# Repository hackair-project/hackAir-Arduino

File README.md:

hackAIR is an EU-funded project aiming to develop an open technology platform for citizen observatories on air quality. Air pollution is an environmental issue with serious health and lifespan implications. However, it remains difficult for citizens to assess their exposure to air pollution and air quality issues in their country. Official air quality sensors are often few and far between, coverage is poor outside cities, and their data is not always easily accessible.

## hackAIR Arduino Library

The hackAIR project provides resources to create your own data collection station using the Arduino platform. The library in this repository aims to support a variety of air quality sensors so anyone with some electronics knowledge can measure air quality at home and optionally submit data to the hackAIR database.

### Why Arduino

> Arduino is an open-source electronics platform based on easy-to-use hardware and software. It's intended for anyone making interactive projects. *-arduino.cc*

The Arduino platform helps create electronic project easy and fun with the only prerequisite being willing to learn and experiment. The hackAIR library takes care of the details so you can get measuring in no time.

### Sending data

While not mandatory, the library provides helpers to send air quality data over the Internet to the hackAIR platform. The official [Ethernet Shield](https://www.arduino.cc/en/Main/ArduinoEthernetShieldV2) is supported alongside the [hackAIR WiFi shield](https://github.com/hackair-project/hackAir-ArduinoWiFi), a DIY option for adding wireless connectivity to your data collection station.

### Supported Sensors

The following sensors are currently supported by the library:
 * [DFRobot PM2.5 Air Quality sensor](http://www.hackair.eu/docs/sensor-support/dfrobot/)
 * [PMS5003](http://www.hackair.eu/docs/pms5003/)
 * [SDS011](http://www.hackair.eu/docs/sds011/)
 * [PPD42NS - Grove sensor by SEEDSTUDIO](http://www.hackair.eu/docs/ppd42ns/)

### Documentation

Official documentation is available at [hackair.eu/docs/](http://www.hackair.eu/docs/). The website is continiously updated with more examples and helpful info.

### Licensing

```
hackAIR Arduino Library
Copyright © 2016-2017 hackAir Consortium

This program is free software: you can redistribute it and/or modify
it under the terms of the GNU Lesser General Public License as published
by the Free Software Foundation, either version 3 of the License, or
(at your option) any later version.

This program is distributed in the hope that it will be useful,
but WITHOUT ANY WARRANTY; without even the implied warranty of
MERCHANTABILITY or FITNESS FOR A PARTICULAR PURPOSE.  See the
GNU Lesser General Public License for more details.

You should have received a copy of the GNU Lesser General Public License
along with this program.  If not, see <http://www.gnu.org/licenses/>.
```

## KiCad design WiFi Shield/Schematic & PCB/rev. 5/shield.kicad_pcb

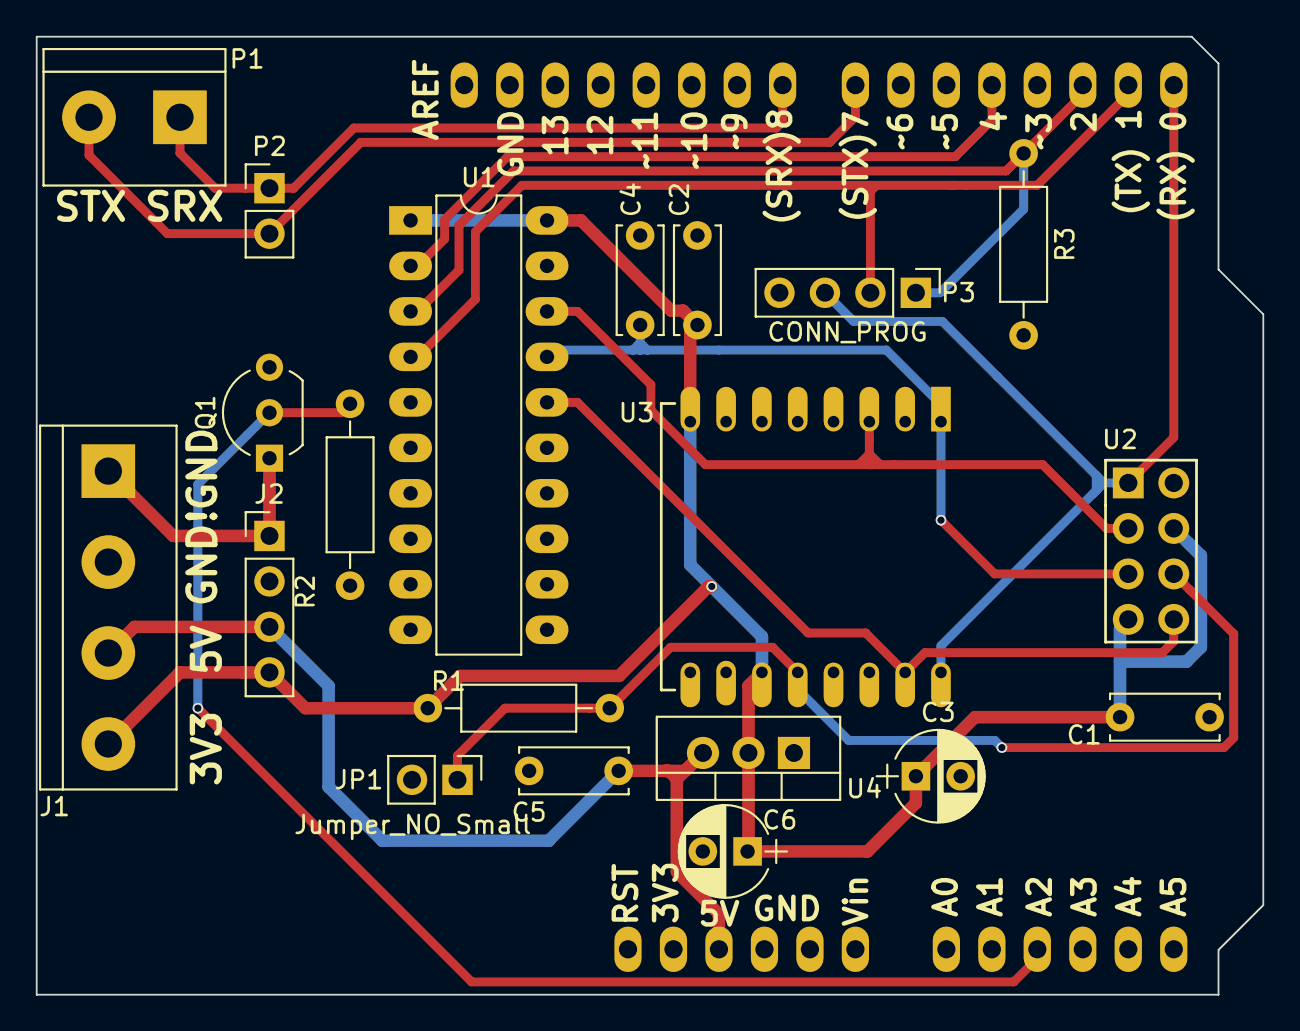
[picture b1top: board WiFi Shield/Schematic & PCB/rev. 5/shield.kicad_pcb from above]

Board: 2 copper layers, 68.5 x 53.5 mm, 21 parts (0 on the bottom side), 15 nets.

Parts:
C1, C4: 10nF; C_Disc_D6.0mm_W2.5mm_P5.00mm
C2, C5: 100nF; C_Disc_D6.0mm_W2.5mm_P5.00mm
C3, C6: 10uF; CP_Radial_D5.0mm_P2.50mm
J1: CONN_POWER; bornier4
J2: CONN_POWER_H; Pin_Header_Straight_1x04_Pitch2.54mm
JP1: Jumper_NO_Small; Pin_Header_Straight_1x02_Pitch2.54mm
P1: CONN_SENSOR_SERIAL; bornier2
P2: CONN_SENSOR_SERIAL_H; Pin_Header_Straight_1x02_Pitch2.54mm
P3: CONN_PROG; Pin_Header_Straight_1x04_Pitch2.54mm
Q1: ZVN4206A; TO-92_Inline_Wide
R1: 1K; R_Axial_DIN0207_L6.3mm_D2.5mm_P10.16mm_Horizontal
R2: 100K; R_Axial_DIN0207_L6.3mm_D2.5mm_P10.16mm_Horizontal
R3: 10k; R_Axial_DIN0207_L6.3mm_D2.5mm_P10.16mm_Horizontal
SHIELD1: ARDUINO_SHIELD; ARDUINO_SHIELD_2_040pins
U1: SN74LVC245A; DIP-20_W7.62mm_LongPads
U2: ESP-01v090; ESP-01
U3: ESP-12
U4: LD1117S33CTR; TO-220_Vertical

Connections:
+3V3: C1.1, C2.1, C3.1, C6.1, J1.4, J2.4, R1.2, U1.1, U1.20, U2.4, U2.7, U3.8, U3.11, U4.2
+5V: C5.1, J1.3, J2.3, SHIELD1.5V, U4.3
/ESP_CS: U1.18, U2.3, U3.3
/ESP_IO_0: JP1.1, R1.1, U2.6, U3.12
/ESP_RST: C4.1, U1.17, U2.5, U3.1
/ESP_RX: U1.16, U2.8, U3.15
/ESP_TX: P3.3, SHIELD1.0, U2.1, U3.16
/MC_CS: SHIELD1.4, U1.2
/MC_RST: P3.1, R3.1, SHIELD1.2, U1.3
/MC_TX: P3.2, SHIELD1.1, U1.4
/SENSOR_RX: P1.1, P2.1, SHIELD1.8
/SENSOR_TX: P1.2, P2.2, SHIELD1.7
/SW_GND_G: Q1.2, R2.1, SHIELD1.AD2
GND: C1.2, C2.2, C3.2, C4.2, C5.2, C6.2, J1.2, J2.2, JP1.2, P3.4, Q1.3, R2.2, R3.2, SHIELD1.GND1, SHIELD1.GND2, SHIELD1.GND3, U1.10, U1.19, U2.2, U3.9, U4.1
unnamed: J1.1, J2.1, Q1.1

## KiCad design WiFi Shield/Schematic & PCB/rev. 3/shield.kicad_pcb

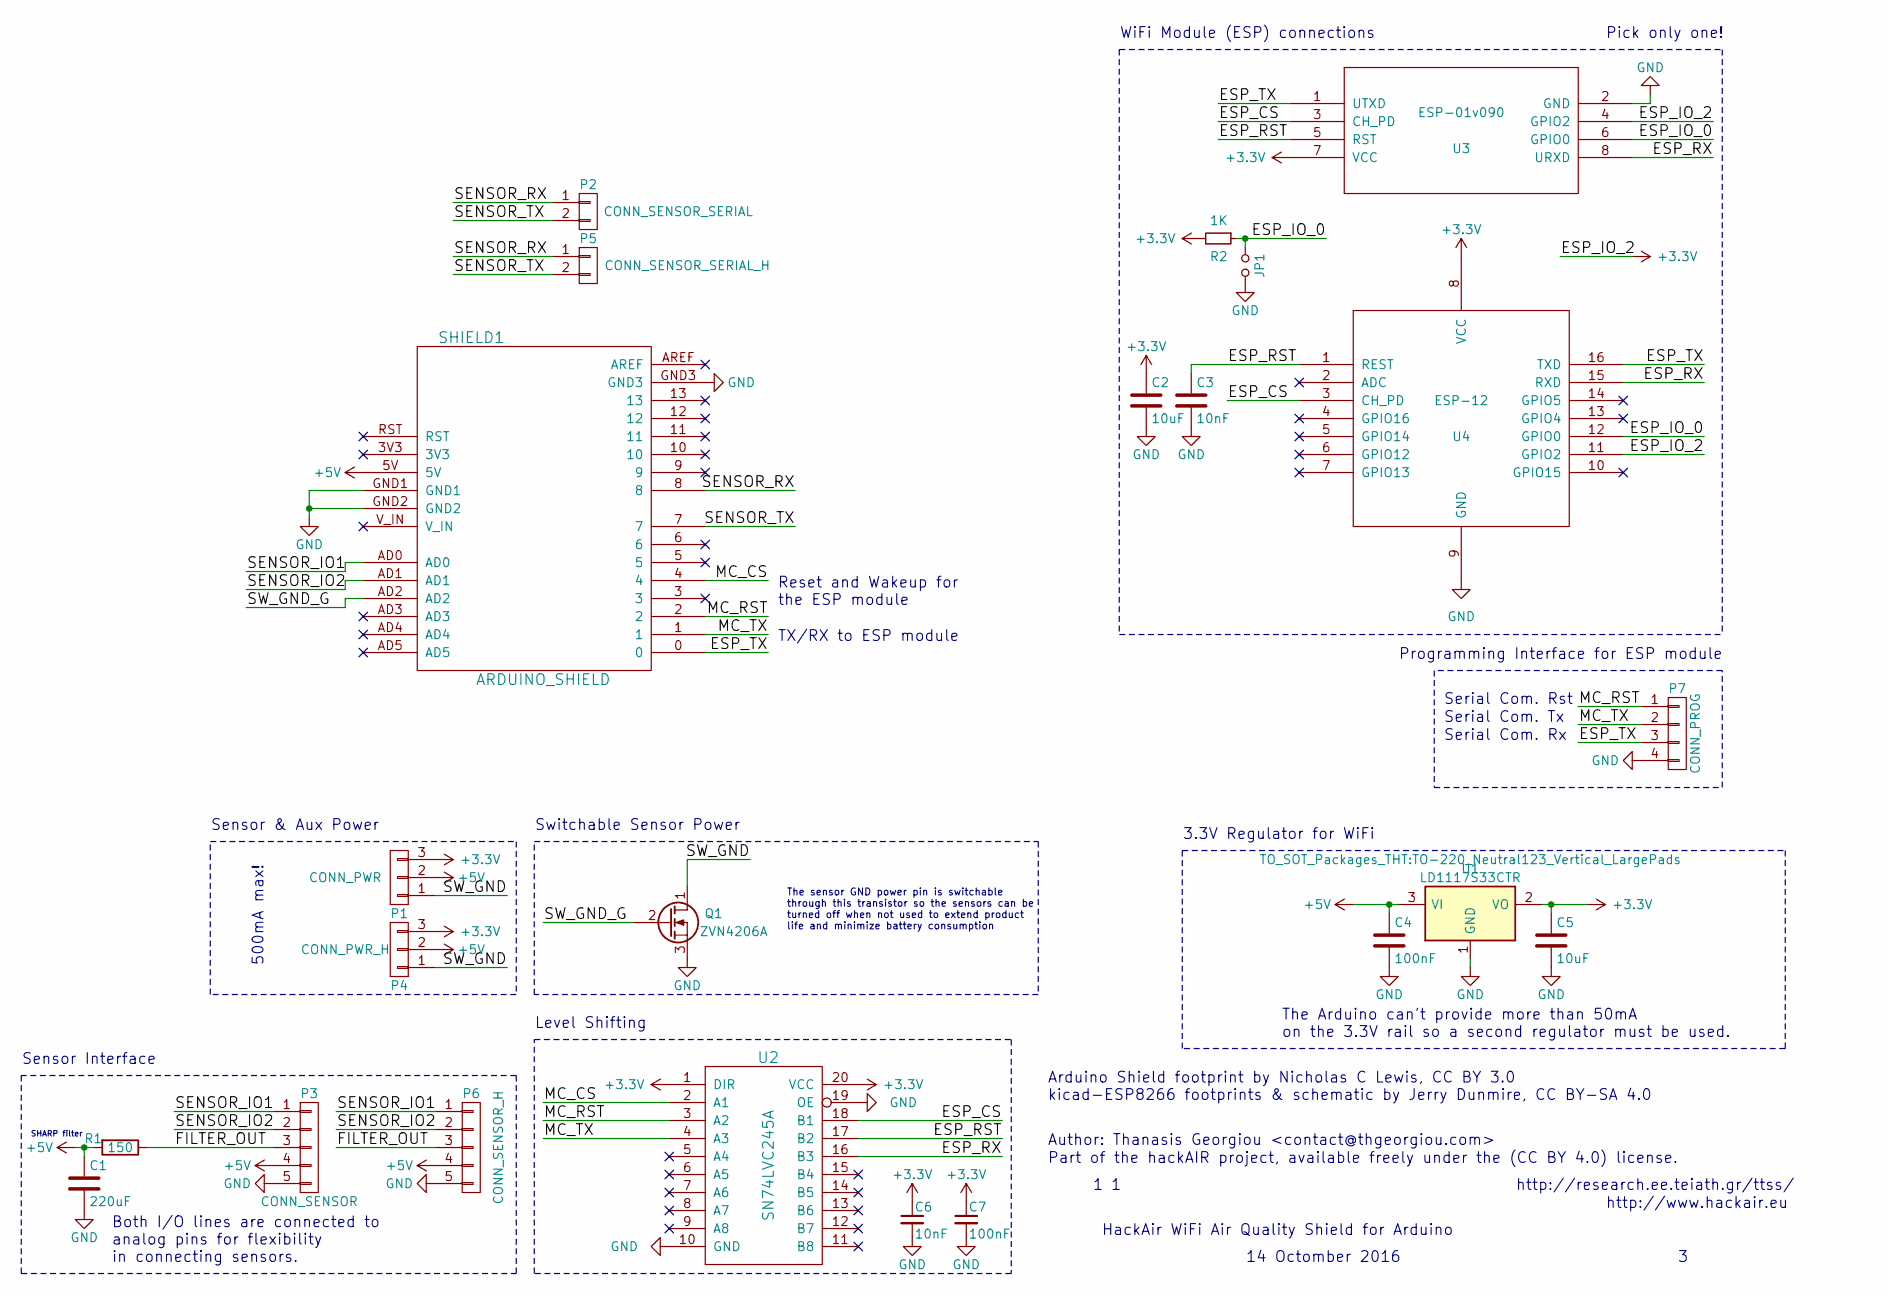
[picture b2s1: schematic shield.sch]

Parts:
C1: 220uF; C_Radial_D6.3_L11.2_P2.5
C2, C5: 10uF; C_Radial_D5_L11_P2.5
C3, C6: 10nF; C_Disc_D6_P5
C4, C7: 100nF; C_Disc_D6_P5
JP1: Jumper_NO_Small; Pin_Header_Straight_1x02
P1: CONN_PWR; bornier3
P2: CONN_SENSOR_SERIAL; bornier2
P3: CONN_SENSOR; bornier5
P4: CONN_PWR_H; Pin_Header_Straight_1x03
P5: CONN_SENSOR_SERIAL_H; Pin_Header_Straight_1x02
P6: CONN_SENSOR_H; Pin_Header_Straight_1x05
P7: CONN_PROG; Pin_Header_Straight_1x04_Pitch2.54mm
Q1: ZVN4206A; TO-92_Inline_Wide
R1: 150; Resistor_Horizontal_RM10mm
R2: 1K; Resistor_Horizontal_RM10mm
SHIELD1: ARDUINO_SHIELD; ARDUINO_SHIELD_2_040pins
U1: LD1117S33CTR; TO-220_Neutral123_Vertical_LargePads
U2: SN74LVC245A; DIP-20_W7.62mm_LongPads
U3: ESP-01v090; ESP-01
U4: ESP-12

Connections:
+3V3: C2.1, C5.1, C6.1, C7.1, P1.3, P4.3, R2.2, U1.2 (VO), U2.1 (DIR), U2.20 (VCC), U3.4 (GPIO2), U3.7 (VCC), U4.8 (VCC), U4.11 (GPIO2)
+5V: C1.1, C4.1, P1.2, P3.4, P4.2, P6.4, R1.2, SHIELD1.5V, U1.3 (VI)
/ESP_CS: U2.18 (B1), U3.3 (CH_PD), U4.3 (CH_PD)
/ESP_IO_0: JP1.1, R2.1, U3.6 (GPIO0), U4.12 (GPIO0)
/ESP_RST: C3.1, U2.17 (B2), U3.5 (RST), U4.1 (REST)
/ESP_RX: U2.16 (B3), U3.8 (URXD), U4.15 (RXD)
/ESP_TX: P7.3, SHIELD1.0, U3.1 (UTXD), U4.16 (TXD)
/FILTER_OUT: P3.3, P6.3, R1.1
/MC_CS: SHIELD1.4, U2.2 (A1)
/MC_RST: P7.1, SHIELD1.2, U2.3 (A2)
/MC_TX: P7.2, SHIELD1.1, U2.4 (A3)
/SENSOR_IO1: P3.1, P6.1, SHIELD1.AD0
/SENSOR_IO2: P3.2, P6.2, SHIELD1.AD1
/SENSOR_RX: P2.1, P5.1, SHIELD1.8
/SENSOR_TX: P2.2, P5.2, SHIELD1.7
/SW_GND: P1.1, P4.1, Q1.1 (D)
/SW_GND_G: Q1.2 (G), SHIELD1.AD2
GND: C1.2, C2.2, C3.2, C4.2, C5.2, C6.2, C7.2, JP1.2, P3.5, P6.5, P7.4, Q1.3 (S), SHIELD1.GND1, SHIELD1.GND2, SHIELD1.GND3, U1.1 (GND), U2.10 (GND), U2.19 (OE), U3.2 (GND), U4.9 (GND)

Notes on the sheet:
The Arduino can't provide more than 50mA on the 3.3V rail so a second regulator must be used.
TX/RX to ESP module
Reset and Wakeup for the ESP module
WiFi Module (ESP) connections
Pick only one!
3.3V Regulator for WiFi
Level Shifting
HackAir WiFi Air Quality Shield for Arduino
14 Octomber 2016
Arduino Shield footprint by Nicholas C Lewis, CC BY 3.0 kicad-ESP8266 footprints & schematic by Jerry Dunmire, CC BY-SA 4.0
Both I/O lines are connected to analog pins for flexibility in connecting sensors.
Sensor Interface
SHARP filter
Part of the hackAIR project, available freely under the (CC BY 4.0) license.
http://research.ee.teiath.gr/ttss/
http://www.hackair.eu
Author: Thanasis Georgiou <contact@thgeorgiou.com>
The sensor GND power pin is switchable through this transistor so the sensors can be turned off when not used to extend product life and minimize battery consumption
Switchable Sensor Power
500mA max!
Sensor & Aux Power
Serial Com. Tx
Serial Com. Rx
Serial Com. Rst
Programming Interface for ESP module

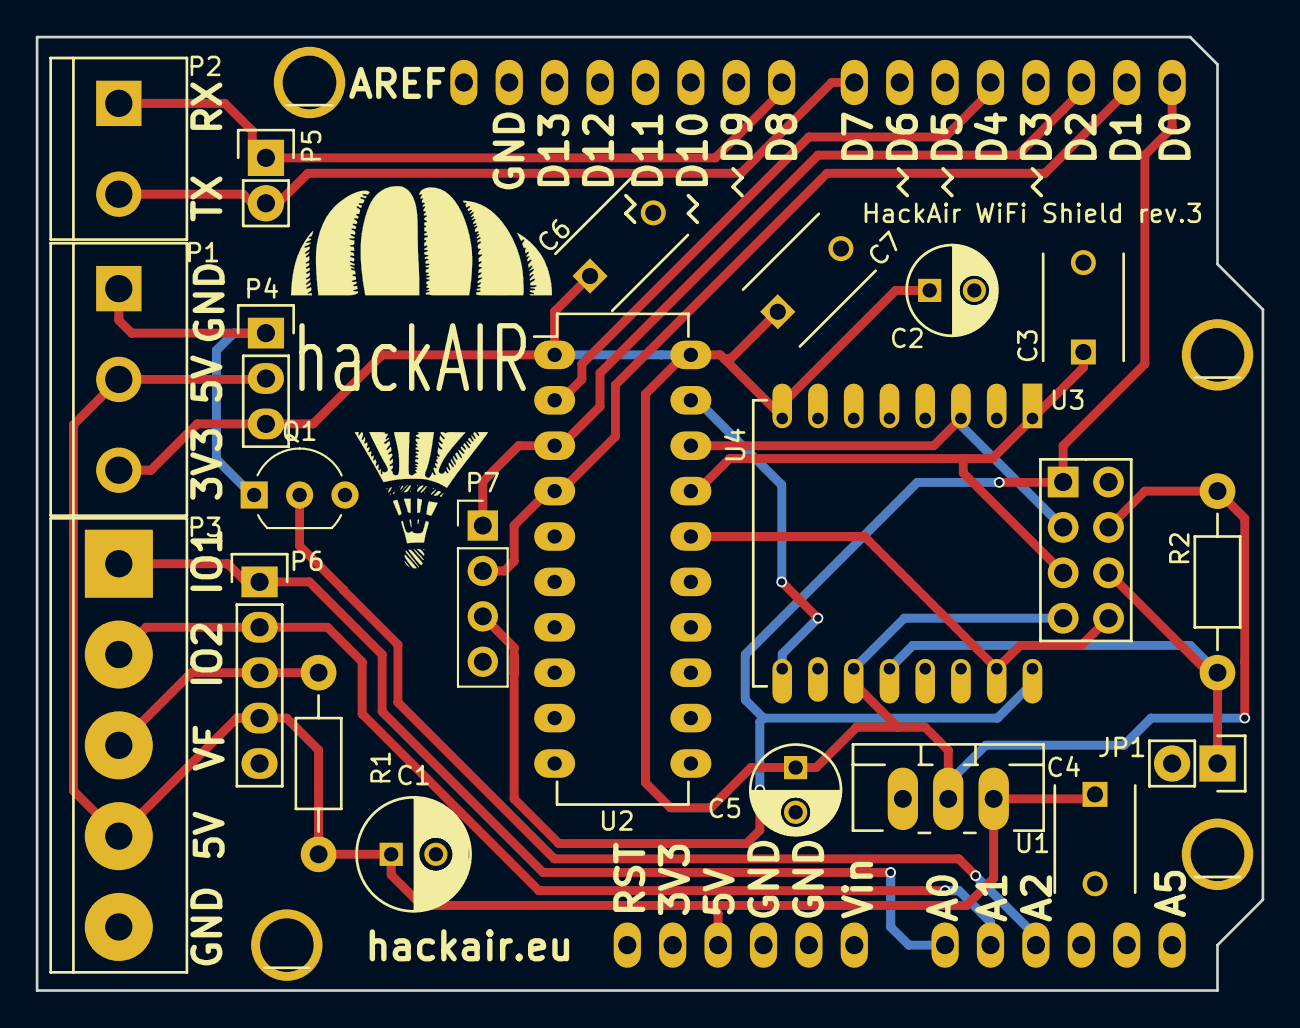
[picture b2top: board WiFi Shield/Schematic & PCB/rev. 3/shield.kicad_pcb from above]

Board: 2 copper layers, 68.6 x 53.3 mm, 27 parts (0 on the bottom side), 18 nets.

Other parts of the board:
HOLE: Pin_Header_Straight_1x01
HOLE#2, HOLE#3, HOLE#4: Pin_Header_Straight_1x01

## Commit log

2016-11-13 Shield - Schematic & PCB Initial Commit
2016-11-21 Shield - Firmware Initial Commit
2016-11-21 Library - Initial Commit
2016-11-22 Library - Fix edge case not handled on refresh()
2016-11-22 Update repo README
2016-12-29 Shield - PCB rev. 3
2016-12-31 Add basic support for Sharp GP2Y1010AU0F
2016-12-31 Add basic support for DN7C3CA006.
    Reading raw data is basically the same as GP2Y1010AU0F.
2017-01-15 Add support for Plantower PMS5003
    This sensor is very similar to the DFRobot one. The serial interface is the same,
    they seem to differ only in physical shape.
2017-01-16 Add support for Shinyei PPD42NS.
    Closes #4.
2017-01-17 Update licensing
    The Arduino library is now licensed under LGPL. The hardware is
    still available in the Public Domain.
2017-02-16 Shield - Use new API version
2017-02-16 Shield - Add 'e+version' command
2017-02-16 Shield - Add script to build firmware image
2017-02-16 Shield - Update Readme
2017-02-16 Library - Add official Ethernet shield support
2017-03-21 Shield - Refactor `send_data()` to be more readable
    Also removed 'hackAir' from the function name, it should be generic (TODO: add command to change the post URL)
2017-03-21 Shield - Make serial command handling more robust
    Fixed:
    - Crashing when no arguments are passed and they are required
    - Ignoring commands when no arguments are passed
    Added:
    - Error message for unknown command
    - Error message for missing arguments
2017-03-21 Shield - Display welcome message to make it clear why the unit is not responding to lua commands
2017-03-21 Shield - Firmware version bump to 0.2.0
2017-03-23 Library - Add hackAirData struct for storing data
2017-04-04 Shield - PCB rev. 4
2017-04-05 Library - Switch sensor data output to the new struct style
2017-04-05 Library - Drop support for the analog sensors from SHARP
2017-04-05 Library - Add ethernet shield support
2017-04-06 Shield - Rename `error` variable to `err` to avoid confusion with the `error()` function of Lua
2017-04-12 Shield - Add build scripts for Arduino upgrade sketch
2017-04-12 Shield - Revision 5
2017-04-12 Shield - Fix welcome message not appearing correctly
2017-04-12 Shield - Fix `e+clearap` command for current NodeMCU version
2017-04-12 Shield - Firmware version bump
2017-04-12 Shield - Fix format of JSON data
2017-04-12 Library - Add ESP Upgrade script for version v0.3.0
2017-04-12 Library - Version bump
2017-04-20 Library - Add an example for sending CSV data through serial
2017-04-26 Library - Switch WiFi to the new hackAirData struct
2017-04-26 Library - hackair.h must be included before the WiFi header
2017-04-26 Remove WiFi shield from this repository
    New home: https://github.com/hackair-project/hackAir-ArduinoWiFi
2017-04-26 Add example with LCD
2017-05-04 Fix URLs
2017-05-07 Use 'canonifyURLs' to fix CSS
2017-05-07 Redirect homepage to first documentation page
2017-05-07 Redirect to the corrent homepage
2017-05-18 Fix API endpoint typo
2017-07-07 Add a function to initialize/clear the hackAirData struct
2017-07-10 Add WiFi shield documentation
2017-07-31 Add production URL, Fix endpoint typo
2017-08-02 Fix broken toplvl URL
2017-09-28 Use HTTP for Ethernet since HTTPS is not supported by the ethernet shield
2017-09-28 Version bump
2017-09-28 Add flashing guide for WiFi shield, update grav theme
2017-09-29 Improve readme
2017-09-29 Bring ESP-update sketch up-to-date with the new firmware
2017-10-02 Ethernet - Fix HTTP header to include "HTTP/1.1"
2017-10-02 Add list of supported sensors to the README
2017-10-04 Add parts list to WiFi shield
2017-10-04 Fix PCB order link
2017-11-01 Add control for the WiFi shield FET
2017-11-05 Improve library and ethernet documentation
2017-11-06 Fix new power management functions not being in the correct namespace
2017-11-06 Fix fault in SDS011 data packet decoding
2017-11-13 Add support for Wemos ESP8266-based boards
2017-11-13 Add native power saving for SDS011
2017-11-14 Add info about powersaving
2017-11-14 Remove references to A2 (FET gate) when on ESP8266
2017-11-14 Switch serial pins on ESP8266 to D6, D7
    D8 is used to control the boot process so flashing the board when the sensor is connected becomes difficult
2017-11-14 Version bump - v0.5.0
2017-11-14 Add guide about serial ports on Windows
2017-11-19 Change example naming scheme
2017-11-19 Add example sketch for resetting the WiFi shield's saved access points
2017-11-19 Remove the license from the Ethernet Simple example
2017-11-19 Add an advanced example for the Ethernet shield (w/ sensor sleep)
2017-11-19 Clean up the Simple WiFi example (fix license, etc)
2017-11-19 Add advanced example for the hackAIR WiFi shield
2017-11-19 Version bump (0.5.1)
2017-11-19 Add WiFi shield example, information about switching WiFi networks
2017-11-25 Add option for humidity compensation
2017-11-27 Add wemos manual
2017-11-27 Resize Wemos photos to be web-friendly
2017-11-27 Fix headings for Wemos manual
2017-11-27 Fix wemos screenshots
2017-11-29 Initial clean up of the Wemos example
2017-11-29 Finalize Wemos example
2017-11-29 Change humidity normalization function to something more tested
2017-12-04 Fix board-manager photo for Wemos
2018-03-12 Add function to average n readings
    Examples currently use `refresh()` to fill the data into a `hackAIRData`
    struct, extract the data into separate variables to calculate the mean
    value and then put the data back into the struct to use the submit function.
    This is kinda clunky and this change aims to provide a better API for something
    commonly used.
2018-03-12 Add `humidityCompensation()` into the hackAIR class
2018-03-12 Use new average measurement API in examples, remove duplicate simple/advanced sketches
2018-03-12 Use new API for reading data in example sketches for nodes without networking
2018-03-28 on error, retry getting valid data from sensor
    I tested with my SDS011 sensor. In error case, the hackAIR system interprets the data as a transmitted 0µg measurement for both PM10 and PM25. This leads to an unrealistic data base!
    Fix: For these cases and as a general improvement of the example, lets examine the error code!
    Note: presumably, the Wemos D1 example should be modified also!
2018-04-01 Send error and tamper fields to server
2018-04-01 Error field in data struct is set to '1' by default
2018-04-01 Retrying measurements for a configurable amount of time
2018-04-01 Reset data struct before measurement
2018-04-01 Perform Humidity compensation only when DHT measurement was successful
2018-05-06 Add a delay after sensor wakup (SDS011)
2018-05-06 Add a delay between average measurements in `readAverageData()`
2018-05-06 Add error codes
2018-05-06 If the humidity sensor fails do not use humidity compensation
    This also uses the new error codes
2018-05-06 Clean up old debug code from Wemos sketch
2018-05-06 Update copyright notice
2018-05-06 Return an error if no values are recorded during `readAverageData`
2018-06-24 Send library version with data (Wemos)
2018-07-17 Use correct field separator in keywords.txt
    The Arduino IDE requires the use of a single true tab separator between the keyword name and identifier. When spaces are used rather than a true tab the keyword is not highlighted.
    Reference:
    https://github.com/arduino/Arduino/wiki/Arduino-IDE-1.5:-Library-specification#keywords
2018-10-11 Update documentation links
    Moved to http://www.hackair.eu/docs/
2018-12-06 Version bump: 1.0.0
2019-01-20 turnOn fix for newer SDS011 sensors
    Should work just as fine for older sensors too which only require single byte to wake up.
2019-01-20 Dynamically set rx and txpin of SoftwareSerial
    _serial made private and as a pointer in hackAIR class for runtime declaration.
    added int _rxPin and _txPIn private members
    added constructor hackAIR::hackAIR(int sensorType, int rxpin, int txpin).
    If the old constructor hackAIR::hackAIR(int sensorType) is called, default rx and txpin values are used. (for backwards compatibility).
    Example usage:
    const int rxpin=12, txpin=13;
2019-12-28 Specify library dependencies in library.properties
    Specifying the library dependencies in the depends field of library.properties causes the Arduino Library Manager (Arduino IDE 1.8.10 and newer) to offer to install any missing dependencies during in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

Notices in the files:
WiFi Shield/Schematic & PCB/rev. 5/shield.kicad_pcb:
kicad0ESP8266 footprints & schematic by Jerry Dunmire, CC BY-SA 4.0
